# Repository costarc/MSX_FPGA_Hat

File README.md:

# MSX_FPGA_Hat
A Cartridge interface that converts MSX 5v signal levels to 3v, exposing an IDC connector for external devices that operates at 3v level.

Interface for MSX computers with level shift conversion to 3.3v. Allow MSX to use FPGA development boards such as Terasic DE0 and DE1 as generic peripherals.

THIS IS WORKING IN PROGRESS. THE BOARD IS BEING TESTED, AND REFERENCE DESIGNS CREATED. ROM and RAM reference designs work well, but as of now I was not able to implement a stable SD Card interface.

## 📖 The Book

This project is **Chapter 10, "MSX FPGA Hat"**, in a book:

**Chips, Code, and Cartridges: Turn Curiosity into Creation with 13 Hands-On Projects, from 8-bit Classics to FPGAs**

It walks through thirteen of my own hardware and software projects, from 8-bit classics to FPGAs, for beginners and curious makers. Each chapter explains how one project works and how to build it, with colour diagrams and real code from its repository.

### 👉 [Get the book on Amazon](https://link.amazon/B013Yaq9y)

<sub>As an Amazon Associate, the author earns from qualifying purchases. Buying through this link
supports these projects at no extra cost to you.</sub>

# Technical Description of the Interface
The interface connects the computer BUS to the FPGA GPIOs, using the flat cable.
The interface should be connected to JP2 of DE1, which corresponds to GPIO_1. This is the GPIO used in all the reference designs in this project. To use JP1 (GPIO_0), all pins must be remapped for the projects.

Address and control signals always flow from the computer to the FPGA - the DIR and /OE signals in U2,U3,U4 and U5 are always asserted (pull-up for bus directoin (Pin 1) and grounded for /OE (pin 19).

For U1, the BUS direction is controlled by the computer read signal (RD_n) in MSX. When read operation is triggered (RD_n = 0), the directon of the data in U1 flows from the FPGA to the computer. At all other times, the data flows from the computer to the FPGA.

U1 has a pull-up in the /OE pin, to keep any output disabled until the FPGA drives this pin low, which should only occur when the FPGA is in fact requested by the computer. Keeping /OE high isolates the computer BUS from anythign happening in the FPGA, which is also important during the boot in the computer.

# Controlling Flow of Data in the Interface
The recommended method to drive the interace signals is as follows:

U1 bus direction (pin 1): no additional implementaton is required - this pin is controlled automatically by the computer according his operations. For example, in the MSX computer, when requesting data from the FPGA, this pin is asserted LOW by RD_n = 0, when sending data it is asserted HIGH because RD_n will be HIGH.

U1 /OE (Output Enable, pin 19): This pin should be put in LOW whenever the FPGA detects that it is being requested - for example, if a ROM is implemented in the FPGA, the address and slot decoding should detect and assert according the GPIO pin /C_U1_D_OE (name was meant to stand for "CI U1, computer Data bus, pin OE).

U2,U3,U4,U5 bus direction: also no need to be concerned - these CIs have fixed bus direction, and constantly asserted HIGH for data to flow from the 74lvc245 bus A to bus B. 
The interface has some pins being used to carry data from the FPG to the computer in these CIs, in which case the routing for such signals was made bringing in input from the GPIO to the bus A, and teh exit in the bus B reouted to the computer.

# Jumpers and Configurations

The limited number of GPIOs in the development board require that we do some compromises in the design.
Some of the less used signals were routed to jumpers, at which point they can be selected to be sent to the FPGA.

J1 allow to select one of /CS1, /CS2 and /CS12 to send to FPGA connector pin 3 (/C_CS_SLT).
J2 allow to select either CLOCK or /RESET signal to send to FPGA connector pin 1 (C_CLK_OR_RST).

# Other Important Considerations

The interface was designed to be compatible with Terasic DEn series of boards. However, these boards present some differences in the GPIOs funtionalities, where some bords (like DE1) have 36 generic I/O pins avaialable fo rinput/output functions, and others like DE0 have four pins dedicated to either input or outputs. This is the case of pins 1 and 3, whch are input only pins, and 19, 21 which are output only.
These differences were already considered in the reference designs, and these pins assigned to functions that will not case problems of limitations to the designs.
If you want to change the pin mapping in the FPGA designs, pay attention to these pins - do not assign functions opposite to the directon they actually work.

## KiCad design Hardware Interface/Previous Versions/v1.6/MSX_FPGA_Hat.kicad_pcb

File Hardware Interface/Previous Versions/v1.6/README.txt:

v1.6 (never sent for fabrication)
- Removed /CS1, CS2, CS12, RFSH, SOUND
- Moded U1 DIR control to jumper (allow enable by /RD or FPGA pin)
- Changed /WAIT & /INT to open collector using transistor
v1.5
- Added pull-up to MSX Data bus lines
- Added missing ground to LM1117
- Fixed bug (changed to 5V) in pull up on wait/int/busdir signals 
v1.4
- Added pull-up to all bus lines input to FPGA (4 x resistor network)
- Added RESET button (reset the MSX)
v1.3
- Updated edge connector (footprint) again, as per MSX standard for edge connector measures
- Moved RFSH & SOUNDIN to Jumper J1 (& removed previous jumpers J3/J4)
- Routed soundin & added R10
- Update silk with new retro games pictures
v1.2
- Changed footprint of PCB to 64mm in the base of cartridge as it was way too tight to insert
- Adde schotky diodes to MSX Input isgnals (Intt/Wait) to have the effect of open collector to isolate these signals from the FPGA when not actively driving them
- Added option to use MSX to power the interface (converted 5V to 3.3v via LD117)
v1.1
- Removed unnecessary xnor gate and jumpers
- Added other jumper to select signals to present to FPGA due to liitations in GPIO pins
- Changed pinout layout to support also Terasic DE0 

v1.0
- Initial version for Terasic DE1

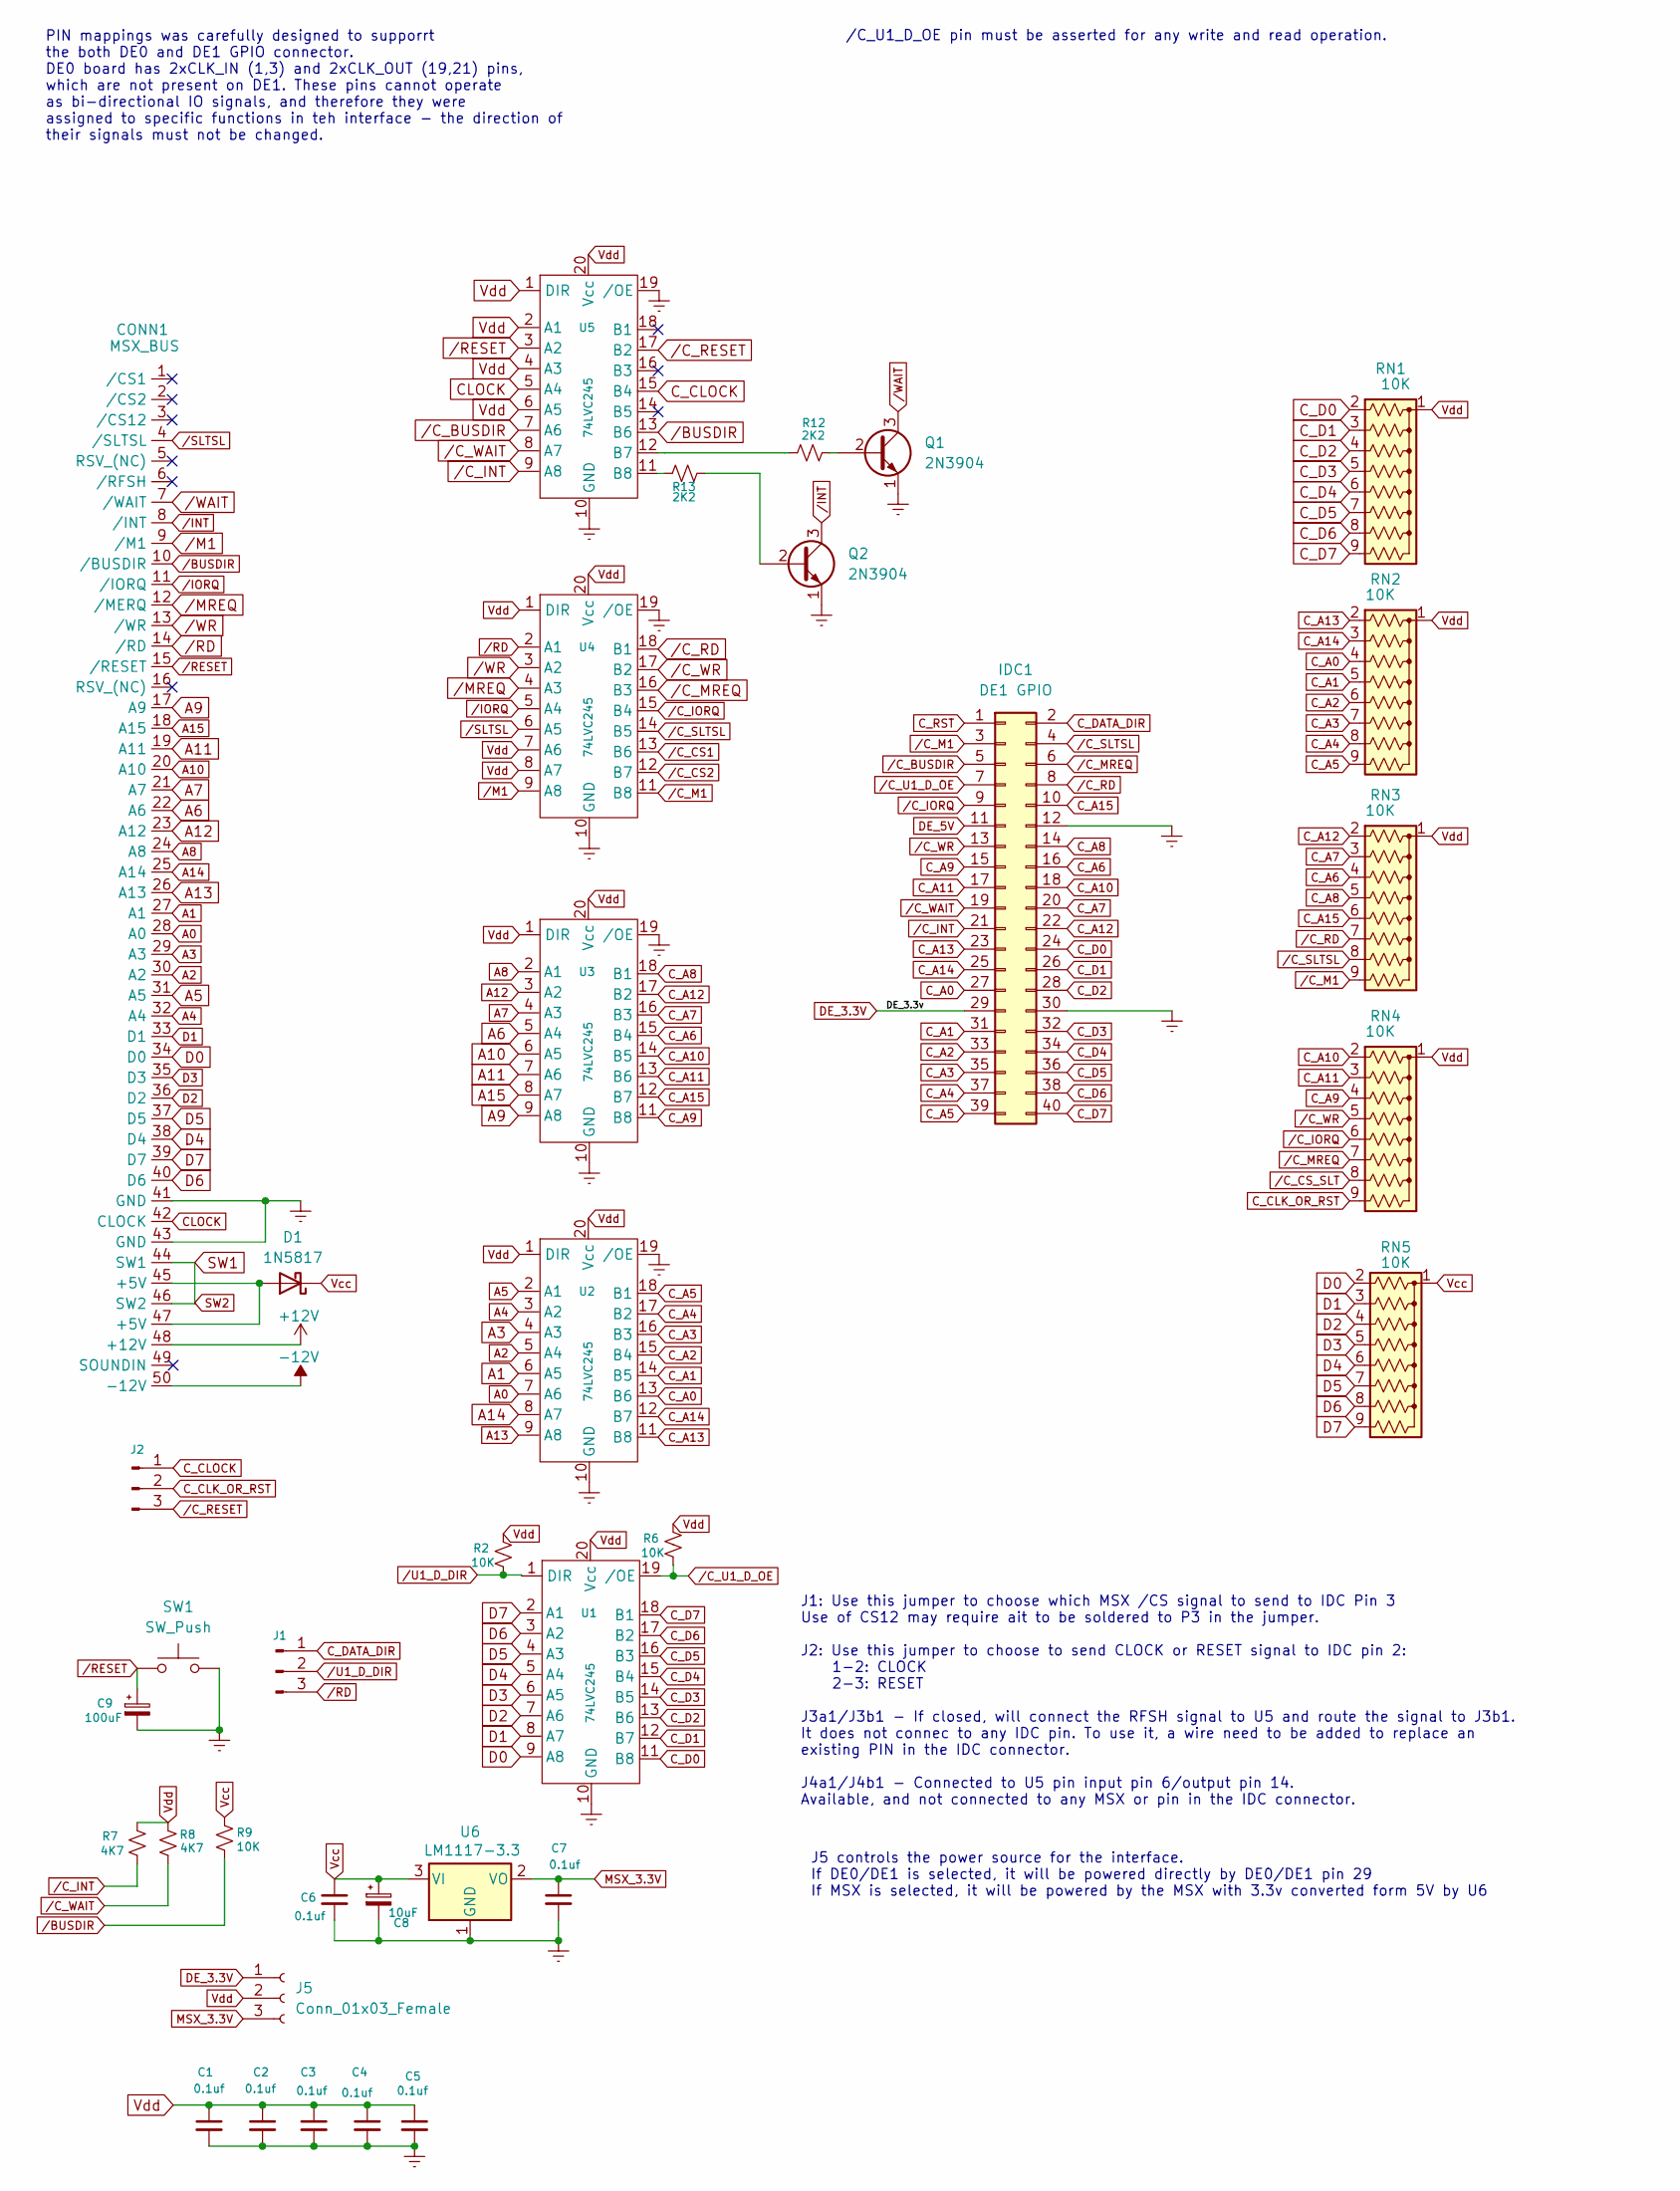
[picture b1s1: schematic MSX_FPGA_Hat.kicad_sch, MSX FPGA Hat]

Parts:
C1, C2, C3, C4, C5, C6, C7: 0.1uf; C_Disc_D3.0mm_W1.6mm_P2.50mm
C8: 10uF; CP_Radial_D6.3mm_P2.50mm
C9: 100uF; CP_Radial_D6.3mm_P2.50mm
CONN1: MSX_BUS; MSX_CART_SW_Official
D1: 1N5817; D_DO-41_SOD81_P10.16mm_Horizontal
IDC1: DE1 GPIO; PinHeader_2x20_P2.54mm_Vertical
J1: J1; PinHeader_1x03_P2.54mm_Vertical
J2: J2; PinHeader_1x03_P2.54mm_Vertical
J5: Conn_01x03_Female; PinHeader_1x03_P2.54mm_Vertical
Q1, Q2: 2N3904; TO-92_Inline
R2, R6, R9: 10K; R_Axial_DIN0207_L6.3mm_D2.5mm_P7.62mm_Horizontal
R7, R8: 4K7; R_Axial_DIN0207_L6.3mm_D2.5mm_P7.62mm_Horizontal
R12, R13: 2K2; R_Axial_DIN0207_L6.3mm_D2.5mm_P7.62mm_Horizontal
RN1, RN2, RN3, RN4, RN5: 10K; R_Array_SIP9
SW1: SW_Push; PinSocket_1x02_P2.54mm_Vertical
U1, U2, U3, U4, U5: 74LVC245; DIP-20_W7.62mm
U6: LM1117-3.3; SOT-223-3_TabPin2

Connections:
+12V: CONN1.48 (+12V)
-12V: CONN1.50 (-12V)
A0: CONN1.28 (A0), U2.7 (A6)
A1: CONN1.27 (A1), U2.6 (A5)
A2: CONN1.30 (A2), U2.5 (A4)
A3: CONN1.29 (A3), U2.4 (A3)
A4: CONN1.32 (A4), U2.3 (A2)
A5: CONN1.31 (A5), U2.2 (A1)
A6: CONN1.22 (A6), U3.5 (A4)
A7: CONN1.21 (A7), U3.4 (A3)
A8: CONN1.24 (A8), U3.2 (A1)
A9: CONN1.17 (A9), U3.9 (A8)
A10: CONN1.20 (A10), U3.6 (A5)
A11: CONN1.19 (A11), U3.7 (A6)
A12: CONN1.23 (A12), U3.3 (A2)
A13: CONN1.26 (A13), U2.9 (A8)
A14: CONN1.25 (A14), U2.8 (A7)
A15: CONN1.18 (A15), U3.8 (A7)
CLOCK: CONN1.42 (CLOCK), U5.5 (A4)
C_A0: IDC1.27, RN2.4 (R3), U2.13 (B6)
C_A1: IDC1.31, RN2.5 (R4), U2.14 (B5)
C_A2: IDC1.33, RN2.6 (R5), U2.15 (B4)
C_A3: IDC1.35, RN2.7 (R6), U2.16 (B3)
C_A4: IDC1.37, RN2.8 (R7), U2.17 (B2)
C_A5: IDC1.39, RN2.9 (R8), U2.18 (B1)
C_A6: IDC1.16, RN3.4 (R3), U3.15 (B4)
C_A7: IDC1.20, RN3.3 (R2), U3.16 (B3)
C_A8: IDC1.14, RN3.5 (R4), U3.18 (B1)
C_A9: IDC1.15, RN4.4 (R3), U3.11 (B8)
C_A10: IDC1.18, RN4.2 (R1), U3.14 (B5)
C_A11: IDC1.17, RN4.3 (R2), U3.13 (B6)
C_A12: IDC1.22, RN3.2 (R1), U3.17 (B2)
C_A13: IDC1.23, RN2.2 (R1), U2.11 (B8)
C_A14: IDC1.25, RN2.3 (R2), U2.12 (B7)
C_A15: IDC1.10, RN3.6 (R5), U3.12 (B7)
C_CLK_OR_RST: J2.2, RN4.9 (R8)
C_CLOCK: J2.1, U5.15 (B4)
C_D0: IDC1.24, RN1.2 (R1), U1.11 (B8)
C_D1: IDC1.26, RN1.3 (R2), U1.12 (B7)
C_D2: IDC1.28, RN1.4 (R3), U1.13 (B6)
C_D3: IDC1.32, RN1.5 (R4), U1.14 (B5)
C_D4: IDC1.34, RN1.6 (R5), U1.15 (B4)
C_D5: IDC1.36, RN1.7 (R6), U1.16 (B3)
C_D6: IDC1.38, RN1.8 (R7), U1.17 (B2)
C_D7: IDC1.40, RN1.9 (R8), U1.18 (B1)
C_DATA_DIR: IDC1.2, J1.1
C_RST: IDC1.1
D0: CONN1.34 (D0), RN5.2 (R1), U1.9 (A8)
D1: CONN1.33 (D1), RN5.3 (R2), U1.8 (A7)
D2: CONN1.36 (D2), RN5.4 (R3), U1.7 (A6)
D3: CONN1.35 (D3), RN5.5 (R4), U1.6 (A5)
D4: CONN1.38 (D4), RN5.6 (R5), U1.5 (A4)
D5: CONN1.37 (D5), RN5.7 (R6), U1.4 (A3)
D6: CONN1.40 (D6), RN5.8 (R7), U1.3 (A2)
D7: CONN1.39 (D7), RN5.9 (R8), U1.2 (A1)
DE_3.3V: IDC1.29, J5.1
DE_5V: IDC1.11
GNDREF: C1.2, C2.2, C3.2, C4.2, C5.2, C6.2, C7.2, C8.2, C9.2, CONN1.41 (GND), CONN1.43 (GND), IDC1.12, IDC1.30, Q1.1 (E), Q2.1 (E), SW1.2, U1.10 (GND), U2.10 (GND), U2.19 (/OE), U3.10 (GND), U3.19 (/OE), U4.10 (GND), U4.19 (/OE), U5.10 (GND), U5.19 (/OE), U6.1 (GND)
MSX_3.3V: C7.1, J5.3, U6.2 (VO)
unnamed: CONN1.45 (+5V), CONN1.47 (+5V), D1.2 (A)
unnamed: Q1.2 (B), R12.1
unnamed: Q2.2 (B), R13.1
unnamed: R12.2, U5.12 (B7)
unnamed: R13.2, U5.11 (B8)
SW1: CONN1.44 (SW1), CONN1.46 (SW2)
Vcc: C6.1, C8.1, D1.1 (K), R9.1, RN5.1 (common), U6.3 (VI)
Vdd: C1.1, C2.1, C3.1, C4.1, C5.1, J5.2, R2.1, R6.1, R7.1, R8.1, RN1.1 (common), RN2.1 (common), RN3.1 (common), RN4.1 (common), U1.20 (Vcc), U2.1 (DIR), U2.20 (Vcc), U3.1 (DIR), U3.20 (Vcc), U4.1 (DIR), U4.7 (A6), U4.8 (A7), U4.20 (Vcc), U5.1 (DIR), U5.2 (A1), U5.4 (A3), U5.6 (A5), U5.20 (Vcc)
/BUSDIR: CONN1.10 (/BUSDIR), R9.2, U5.13 (B6)
/C_BUSDIR: IDC1.5, U5.7 (A6)
/C_CS1: U4.13 (B6)
/C_CS2: U4.12 (B7)
/C_CS_SLT: RN4.8 (R7)
/C_INT: IDC1.21, R7.2, U5.9 (A8)
/C_IORQ: IDC1.9, RN4.6 (R5), U4.15 (B4)
/C_M1: IDC1.3, RN3.9 (R8), U4.11 (B8)
/C_MREQ: IDC1.6, RN4.7 (R6), U4.16 (B3)
/C_RD: IDC1.8, RN3.7 (R6), U4.18 (B1)
/C_RESET: J2.3, U5.17 (B2)
/C_SLTSL: IDC1.4, RN3.8 (R7), U4.14 (B5)
/C_U1_D_OE: IDC1.7, R6.2, U1.19 (/OE)
/C_WAIT: IDC1.19, R8.2, U5.8 (A7)
/C_WR: IDC1.13, RN4.5 (R4), U4.17 (B2)
/INT: CONN1.8 (/INT), Q2.3 (C)
/IORQ: CONN1.11 (/IORQ), U4.5 (A4)
/M1: CONN1.9 (/M1), U4.9 (A8)
/MREQ: CONN1.12 (/MERQ), U4.4 (A3)
/RD: CONN1.14 (/RD), J1.3, U4.2 (A1)
/RESET: C9.1, CONN1.15 (/RESET), SW1.1, U5.3 (A2)
/SLTSL: CONN1.4 (/SLTSL), U4.6 (A5)
/U1_D_DIR: J1.2, R2.2, U1.1 (DIR)
/WAIT: CONN1.7 (/WAIT), Q1.3 (C)
/WR: CONN1.13 (/WR), U4.3 (A2)

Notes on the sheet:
PIN mappings was carefully designed to supporrt the both DE0 and DE1 GPIO connector. DE0 board has 2xCLK_IN (1,3) and 2xCLK_OUT (19,21) pins, which are not present on DE1. These pins cannot operate as bi-directional IO signals, and therefore they were assigned to specific functions in teh interface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
/C_U1_D_OE pin must be asserted for any write and read operation.
J1: Use this jumper to choose which MSX /CS signal to send to IDC Pin 3 Use of CS12 may require ait to be soldered to P3 in the jumper. J2: Use this jumper to choose to send CLOCK or RESET signal to IDC pin 2: 1-2: CLOCK 2-3: RESET J3a1/J3b1 - If closed, will connect the RFSH signal to U5 and route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
J5 controls the power source for the interface. If DE0/DE1 is selected, it will be powered directly by DE0/DE1 pin 29 If MSX is selected, it will be powered by the MSX with 3.3v converted form 5V by U6

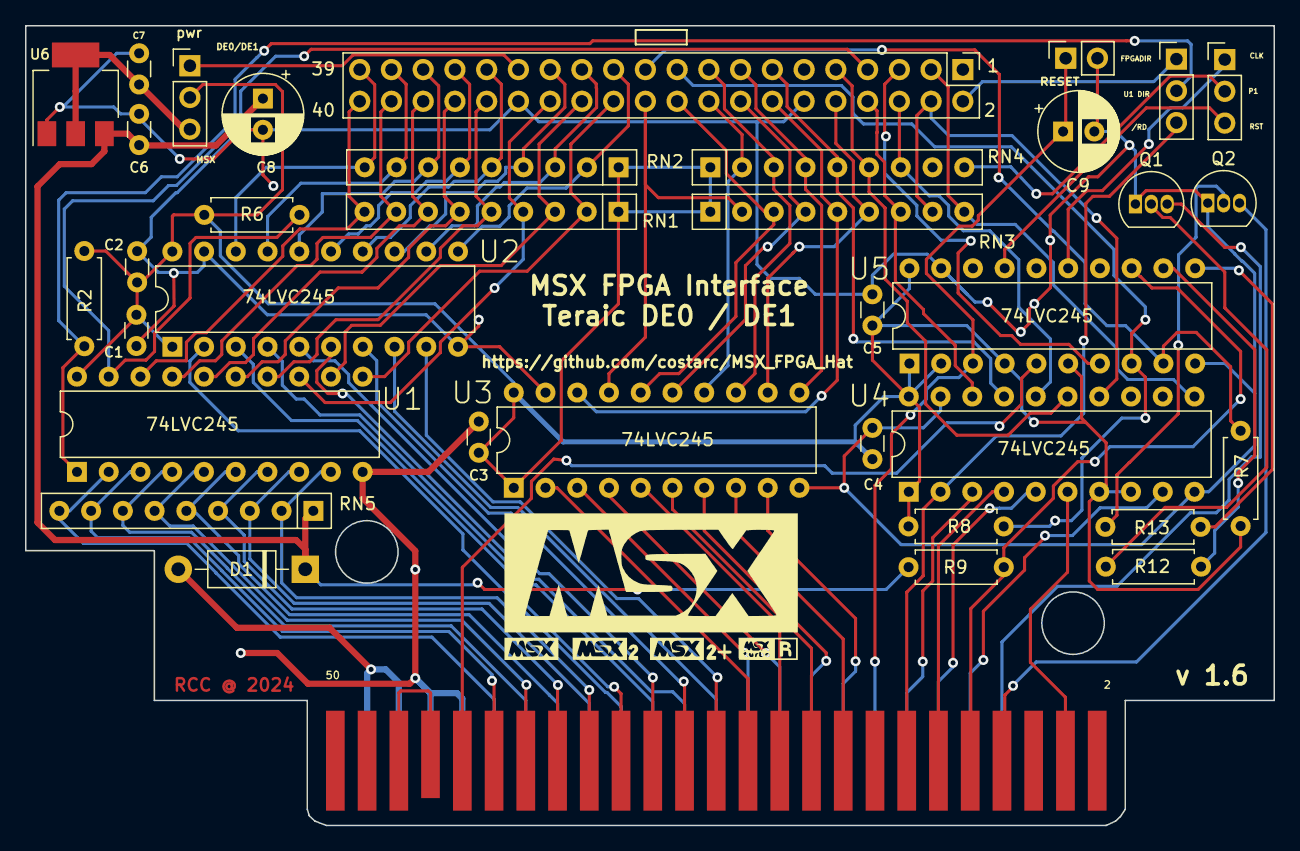
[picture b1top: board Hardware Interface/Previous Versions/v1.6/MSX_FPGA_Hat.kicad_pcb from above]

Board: 2 copper layers, 99.9 x 64.0 mm, 36 parts (0 on the bottom side), 85 nets.

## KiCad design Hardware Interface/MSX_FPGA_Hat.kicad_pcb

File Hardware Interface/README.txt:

v2.1 This versin breaks compatibility with all previous interfaces.
- Redesigned the schema & PCB with change of signals assignments
- MSX Address bus now sharing a 8 bits bus in the FPGA (fsm decode the low/high bits)
- Removed RESET signal circuitry
- Added Audio circuitry from Wondertang (Luis Antoniosi project)
- Updated /int and /wait signals to open collector outputs using transistors
- added test points to /wait, /int and /busdir
- Jumper added to select between MSX Refresh and CS2 signals
- change in silk layout
- Added audiojack for future use
- Connected MSX SOUND to the FPGA

v2.0 Lost track of the changes in this release.

v1.6 (never sent for fabrication)
- Removed /CS1, CS2, CS12, RFSH, SOUND
- Moded U1 DIR control to jumper (allow enable by /RD or FPGA pin)
- Changed /WAIT & /INT to open collector using transistor
v1.5
- Added pull-up to MSX Data bus lines
- Added missing ground to LM1117
- Fixed bug (changed to 5V) in pull up on wait/int/busdir signals 
v1.4
- Added pull-up to all bus lines input to FPGA (4 x resistor network)
- Added RESET button (reset the MSX)
v1.3
- Updated edge connector (footprint) again, as per MSX standard for edge connector measures
- Moved RFSH & SOUNDIN to Jumper J1 (& removed previous jumpers J3/J4)
- Routed soundin & added R10
- Update silk with new retro games pictures
v1.2
- Changed footprint of PCB to 64mm in the base of cartridge as it was way too tight to insert
- Adde schotky diodes to MSX Input isgnals (Intt/Wait) to have the effect of open collector to isolate these signals from the FPGA when not actively driving them
- Added option to use MSX to power the interface (converted 5V to 3.3v via LD117)
v1.1
- Removed unnecessary xnor gate and jumpers
- Added other jumper to select signals to present to FPGA due to liitations in GPIO pins
- Changed pinout layout to support also Terasic DE0 

v1.0
- Initial version for Terasic DE1

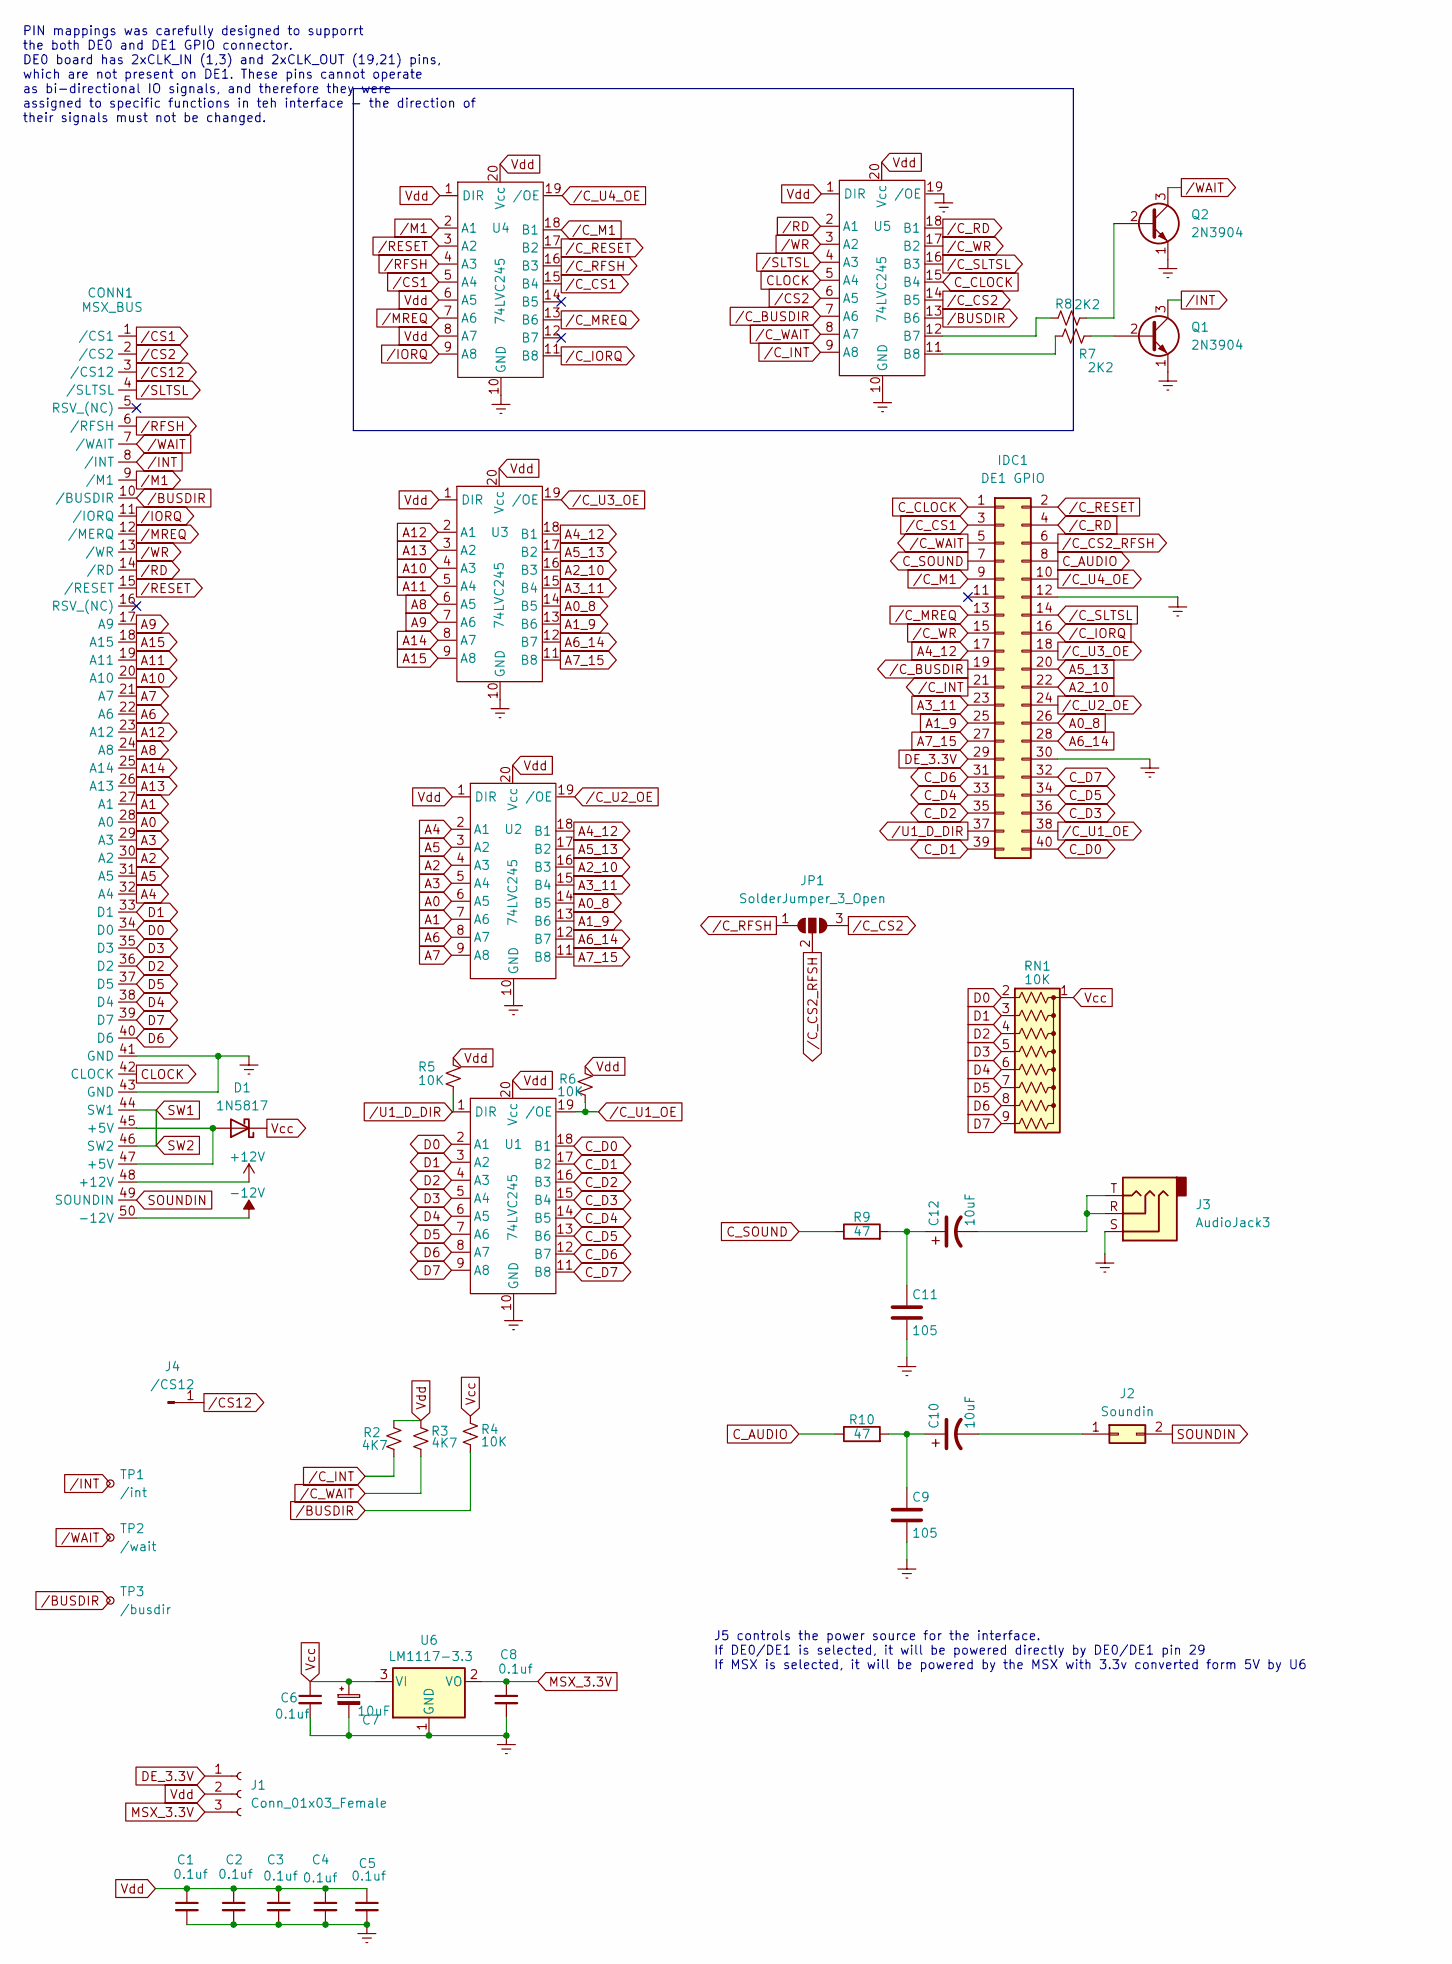
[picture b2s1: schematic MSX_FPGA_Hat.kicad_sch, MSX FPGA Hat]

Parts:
C1, C2, C3, C4, C5, C6, C8: 0.1uf; C_Disc_D3.0mm_W1.6mm_P2.50mm
C7, C10, C12: 10uF; CP_Radial_D5.0mm_P2.00mm
C9, C11: 105; C_Disc_D5.0mm_W2.5mm_P2.50mm
CONN1: MSX_BUS; MSX_CART_SW_Official
D1: 1N5817; D_DO-41_SOD81_P10.16mm_Horizontal
IDC1: DE1 GPIO; PinHeader_2x20_P2.54mm_Vertical
J1: Conn_01x03_Female; PinHeader_1x03_P2.54mm_Vertical
J2: Soundin; PinHeader_2x01_P2.54mm_Vertical
J3: AudioJack3; Jack_3.5mm_CUI_SJ1-3533NG_Horizontal
J4: /CS12; PinHeader_1x01_P2.54mm_Vertical
JP1: SolderJumper_3_Open; SolderJumper-3_P2.0mm_Open_TrianglePad1.0x1.5mm
Q1, Q2: 2N3904; TO-92_Wide
R2, R3: 4K7; R_Axial_DIN0207_L6.3mm_D2.5mm_P10.16mm_Horizontal
R4, R5, R6: 10K; R_Axial_DIN0207_L6.3mm_D2.5mm_P10.16mm_Horizontal
R7, R8: 2K2; R_Axial_DIN0207_L6.3mm_D2.5mm_P10.16mm_Horizontal
R9, R10: 47; R_Axial_DIN0207_L6.3mm_D2.5mm_P10.16mm_Horizontal
RN1: 10K; R_Array_SIP9
TP1: /int; TestPoint_Loop_D1.80mm_Drill1.0mm_Beaded
TP2: /wait; TestPoint_Loop_D1.80mm_Drill1.0mm_Beaded
TP3: /busdir; TestPoint_Loop_D1.80mm_Drill1.0mm_Beaded
U1, U2, U3, U4, U5: 74LVC245; DIP-20_W7.62mm
U6: LM1117-3.3; SOT-223-3_TabPin2

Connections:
+12V: CONN1.48 (+12V)
-12V: CONN1.50 (-12V)
A0: CONN1.28 (A0), U2.6 (A5)
A0_8: IDC1.26, U2.14 (B5), U3.14 (B5)
A1: CONN1.27 (A1), U2.7 (A6)
A1_9: IDC1.25, U2.13 (B6), U3.13 (B6)
A2: CONN1.30 (A2), U2.4 (A3)
A2_10: IDC1.22, U2.16 (B3), U3.16 (B3)
A3: CONN1.29 (A3), U2.5 (A4)
A3_11: IDC1.23, U2.15 (B4), U3.15 (B4)
A4: CONN1.32 (A4), U2.2 (A1)
A4_12: IDC1.17, U2.18 (B1), U3.18 (B1)
A5: CONN1.31 (A5), U2.3 (A2)
A5_13: IDC1.20, U2.17 (B2), U3.17 (B2)
A6: CONN1.22 (A6), U2.8 (A7)
A6_14: IDC1.28, U2.12 (B7), U3.12 (B7)
A7: CONN1.21 (A7), U2.9 (A8)
A7_15: IDC1.27, U2.11 (B8), U3.11 (B8)
A8: CONN1.24 (A8), U3.6 (A5)
A9: CONN1.17 (A9), U3.7 (A6)
A10: CONN1.20 (A10), U3.4 (A3)
A11: CONN1.19 (A11), U3.5 (A4)
A12: CONN1.23 (A12), U3.2 (A1)
A13: CONN1.26 (A13), U3.3 (A2)
A14: CONN1.25 (A14), U3.8 (A7)
A15: CONN1.18 (A15), U3.9 (A8)
CLOCK: CONN1.42 (CLOCK), U5.5 (A4)
C_AUDIO: IDC1.8, R10.1
C_CLOCK: IDC1.1, U5.15 (B4)
C_D0: IDC1.40, U1.18 (B1)
C_D1: IDC1.39, U1.17 (B2)
C_D2: IDC1.35, U1.16 (B3)
C_D3: IDC1.36, U1.15 (B4)
C_D4: IDC1.33, U1.14 (B5)
C_D5: IDC1.34, U1.13 (B6)
C_D6: IDC1.31, U1.12 (B7)
C_D7: IDC1.32, U1.11 (B8)
C_SOUND: IDC1.7, R9.1
D0: CONN1.34 (D0), RN1.2 (R1), U1.2 (A1)
D1: CONN1.33 (D1), RN1.3 (R2), U1.3 (A2)
D2: CONN1.36 (D2), RN1.4 (R3), U1.4 (A3)
D3: CONN1.35 (D3), RN1.5 (R4), U1.5 (A4)
D4: CONN1.38 (D4), RN1.6 (R5), U1.6 (A5)
D5: CONN1.37 (D5), RN1.7 (R6), U1.7 (A6)
D6: CONN1.40 (D6), RN1.8 (R7), U1.8 (A7)
D7: CONN1.39 (D7), RN1.9 (R8), U1.9 (A8)
DE_3.3V: IDC1.29, J1.1
GNDREF: C1.2, C2.2, C3.2, C4.2, C5.2, C6.2, C7.2, C8.2, C9.2, C11.2, CONN1.41 (GND), CONN1.43 (GND), IDC1.12, IDC1.30, J3.S, Q1.1 (E), Q2.1 (E), U1.10 (GND), U2.10 (GND), U3.10 (GND), U4.10 (GND), U5.10 (GND), U5.19 (/OE), U6.1 (GND)
MSX_3.3V: C8.1, J1.3, U6.2 (VO)
unnamed: C9.1, C10.1, R10.2
unnamed: C11.1, C12.1, R9.2
unnamed: C12.2, J3.R, J3.T
unnamed: CONN1.45 (+5V), CONN1.47 (+5V), D1.2 (A)
unnamed: C10.2, J2.1
unnamed: Q1.2 (B), R7.1
unnamed: Q2.2 (B), R8.1
unnamed: R8.2, U5.12 (B7)
unnamed: R7.2, U5.11 (B8)
SOUNDIN: CONN1.49 (SOUNDIN), J2.2
SW1: CONN1.44 (SW1), CONN1.46 (SW2)
Vcc: C6.1, C7.1, D1.1 (K), R4.1, RN1.1 (common), U6.3 (VI)
Vdd: C1.1, C2.1, C3.1, C4.1, C5.1, J1.2, R2.1, R3.1, R5.1, R6.1, U1.20 (Vcc), U2.1 (DIR), U2.20 (Vcc), U3.1 (DIR), U3.20 (Vcc), U4.1 (DIR), U4.6 (A5), U4.8 (A7), U4.20 (Vcc), U5.1 (DIR), U5.20 (Vcc)
/BUSDIR: CONN1.10 (/BUSDIR), R4.2, TP3.1 (1_1), U5.13 (B6)
/CS1: CONN1.1 (/CS1), U4.5 (A4)
/CS2: CONN1.2 (/CS2), U5.6 (A5)
/CS12: CONN1.3 (/CS12), J4.1 (Pin_1_1)
/C_BUSDIR: IDC1.19, U5.7 (A6)
/C_CS1: IDC1.3, U4.15 (B4)
/C_CS2: JP1.3 (B), U5.14 (B5)
/C_CS2_RFSH: IDC1.6, JP1.2 (C)
/C_INT: IDC1.21, R2.2, U5.9 (A8)
/C_IORQ: IDC1.16, U4.11 (B8)
/C_M1: IDC1.9, U4.18 (B1)
/C_MREQ: IDC1.13, U4.13 (B6)
/C_RD: IDC1.4, U5.18 (B1)
/C_RESET: IDC1.2, U4.17 (B2)
/C_RFSH: JP1.1 (A), U4.16 (B3)
/C_SLTSL: IDC1.14, U5.16 (B3)
/C_U1_OE: IDC1.38, R6.2, U1.19 (/OE)
/C_U2_OE: IDC1.24, U2.19 (/OE)
/C_U3_OE: IDC1.18, U3.19 (/OE)
/C_U4_OE: IDC1.10, U4.19 (/OE)
/C_WAIT: IDC1.5, R3.2, U5.8 (A7)
/C_WR: IDC1.15, U5.17 (B2)
/INT: CONN1.8 (/INT), Q1.3 (C), TP1.1 (1_1)
/IORQ: CONN1.11 (/IORQ), U4.9 (A8)
/M1: CONN1.9 (/M1), U4.2 (A1)
/MREQ: CONN1.12 (/MERQ), U4.7 (A6)
/RD: CONN1.14 (/RD), U5.2 (A1)
/RESET: CONN1.15 (/RESET), U4.3 (A2)
/RFSH: CONN1.6 (/RFSH), U4.4 (A3)
/SLTSL: CONN1.4 (/SLTSL), U5.4 (A3)
/U1_D_DIR: IDC1.37, R5.2, U1.1 (DIR)
/WAIT: CONN1.7 (/WAIT), Q2.3 (C), TP2.1 (1_1)
/WR: CONN1.13 (/WR), U5.3 (A2)

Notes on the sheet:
PIN mappings was carefully designed to supporrt the both DE0 and DE1 GPIO connector. DE0 board has 2xCLK_IN (1,3) and 2xCLK_OUT (19,21) pins, which are not present on DE1. These pins cannot operate as bi-directional IO signals, and therefore they were assigned to specific functions in teh interface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
J5 controls the power source for the interface. If DE0/DE1 is selected, it will be powered directly by DE0/DE1 pin 29 If MSX is selected, it will be powered by the MSX with 3.3v converted form 5V by U6

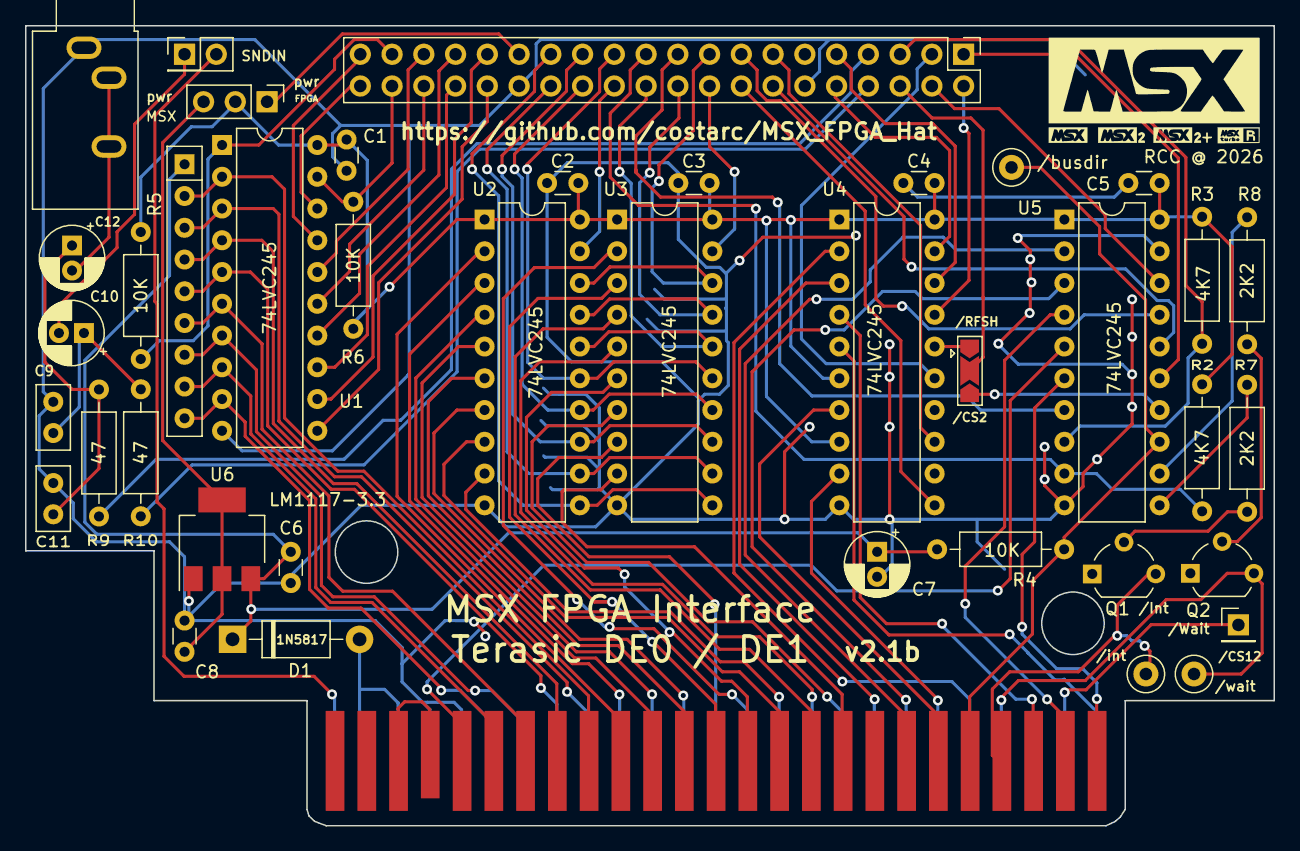
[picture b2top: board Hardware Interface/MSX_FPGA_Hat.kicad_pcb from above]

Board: 2 copper layers, 99.9 x 64.0 mm, 41 parts (0 on the bottom side), 93 nets.

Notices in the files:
Reference Designs (Revised)/Altera DE0 Projects/MultiCart/MultiCart.qsf:
Copyright (C) 1991-2013 Altera Corporation
